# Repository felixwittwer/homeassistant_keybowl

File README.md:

<br>

<div align="center">

 &nbsp; &nbsp; 

</div>

<br>

# homeassistant_keybowl
a smart bowl for your keys with Homeassistant integration and a display to show simple dashoards.

## About the project

This project is smart keybowl where you can toss all your keys into and it will show you some interesting stuff from your Homeassistant instance. It simply hits you with the information you need when leaving home or comming back. The shown dashboards are custom for each user and are recognised by the RFID tag on each keychain.

The Keybowl should speed up your everyday routine by presenting you all the information you might have to look up in some app on your phone. For me personally my dashboard will contain a short version of the days timetable for school and its current changes for the day. When comming home it will probably display some stats of my servers.

The Keybowl siply will be a smart everday helper to make my and the life of others a bit easier and reduce the time you have to look up some information on your phone.

## The Project

### PCB

Be aware that some parts on the rende will not be populated on the PCB because they are not really needed but may be in the future or while I am building the project so for futureprovness the are on in the pcb design and in the rendered images. Have a look at the BOM so se which parts are ment and be aware to bridge the if they are not populated.

### complete assembly

A screenshot of the whole project. Sorry no beautiful render fusions standard wood textures look just ugly :(.

### CAD 

All CAD files can be found inside the [cad](./cad/) directory

[keybowl_complete](./cad/Keybowl%20complete.step) is the whole project and the other files are individual parts of the complete project.

### Firmware

Detailed instructions on how to setup the firmware can be found inside the [firmware folders README](./firmware/README.md)

## BOM

### Aliexpress (for Highway)

**total:** 141.60 USD

| part name | amount | price | link | note |
| --------- | ------ | ----- | ---- | ---- |
| UHF RFID Module 1dbi 35x35mm | 1 | 39.27 USD | https://de.aliexpress.com/item/1005008307223636.html?spm=a2g0o.productlist.main.2.3a2056acCbDovs&algo_pvid=561ac428-5895-4565-92d7-d20539900a0c&pdp_ext_f=%7B%22order%22%3A%228%22%2C%22eval%22%3A%221%22%7D&utparam-url=scene%3Asearch%7Cquery_from%3A | |
| 4.2inch e-paper | 1 | 29.38 USD | https://de.aliexpress.com/item/1005005825856739.html?spm=a2g0o.productlist.main.11.398af4a457pUEA&algo_pvid=a1b8dab7-90ac-46bd-aca0-fde6fcd30138&pdp_ext_f=%7B%22order%22%3A%2213%22%2C%22eval%22%3A%221%22%7D&utparam-url=scene%3Asearch%7Cquery_from%3A | would have liked to choose another one but waveshare has the best documentation and if you decide to upgrade the displays have the same footprint (upgrading from 4 grayscale to black/white/red possible)|
| Raspberry Pi Zero 2 W | 1 | 20.57 USD | https://de.aliexpress.com/item/1005008147614202.html?spm=a2g0o.productlist.main.9.1e3f432ciKsp9W&algo_pvid=32a8750d-1fe9-43b5-99b0-1ed1efdb7aec&pdp_ext_f=%7B%22order%22%3A%22141%22%2C%22eval%22%3A%221%22%7D&utparam-url=scene%3Asearch%7Cquery_from%3A | Pi Zero needed because of Homeassistant integration and connectivity (ESP32-S3 can't quite manage all this stuff together) |
| RFID tags | 5pcs | 0.99 USD | https://de.aliexpress.com/item/1005008292479936.html?spm=a2g0o.productlist.main.45.186a419cIs6EWx&algo_pvid=f2a1d2c4-8d39-4e0e-816f-0145ab5a5fc3&pdp_ext_f=%7B%22order%22%3A%2224%22%2C%22eval%22%3A%221%22%7D&utparam-url=scene%3Asearch%7Cquery_from%3A
| keyswitches | 6 | 1.19 USD | https://de.aliexpress.com/item/1005005371211477.html?spm=a2g0o.productlist.main.6.79e64294kL6s5H&algo_pvid=e22f25ac-00f0-4e9f-a177-d081d068b5ac&pdp_ext_f=%7B%22order%22%3A%2213%22%2C%22eval%22%3A%221%22%7D&utparam-url=scene%3Asearch%7Cquery_from%3A | come as 10 pcs set |
| basic DSA Keycaps | 6 | 1.19 USD | https://de.aliexpress.com/item/1005006005905021.html?spm=a2g0o.productlist.main.11.3fe97aeaDABDMY&algo_pvid=8be567c0-1498-4e45-9ebd-240fe64a8e61&pdp_ext_f=%7B%22order%22%3A%22525%22%2C%22eval%22%3A%221%22%7D&utparam-url=scene%3Asearch%7Cquery_from%3A | come as 20 pcs set |
| PCB and PCBA | 1 | ~ 50 USD |  https://jlcpcb.com/ | price is subject to JLCs review |

**--- PCB Assembly stuff if you want to populate yourself (prices from JLC PCBA) ---**
| part name | amount | price | link | note |
| --------- | ------ | ----- | ---- | ---- |
| capacitor 0.1 uF | 9 | $0.1254 | https://jlcpcb.com/partdetail/C30926 | ---- |
| WS2812B LEDs | 9 | $2.3471 | https://jlcpcb.com/partdetail/C2843785 | ---- |
| diodes | 6 | $0.4644 | https://jlcpcb.com/partdetail/C24372 | ---- |
| | total | 2,9369 USD

<br>
optional parts (will not be populated) keep in mind to bridge footprints

| part name | amount | price | link | note |
| --------- | ------ | ----- | ---- | ---- |
| capacitor 10uF  | 1 | $0.1098 | https://jlcpcb.com/partdetail/C39060 | ---- |
| Levelshifter 74AHCT1G125 | 1 | $0.3820 | https://jlcpcb.com/partdetail/C842287 | ---- |
| Resistor 470 ohm | 9 | $0.0300 | https://jlcpcb.com/partdetail/C21266 | ---- |
| usb-c connector | 1 | 0.99 USD | https://de.aliexpress.com/item/1005008164395076.html?spm=a2g0o.productlist.main.5.3a0390d4i1qG9U&algo_pvid=b5963a54-6f39-4deb-8dc8-244e51b0128a&pdp_ext_f=%7B%22order%22%3A%2252%22%2C%22eval%22%3A%221%22%7D&utparam-url=scene%3Asearch%7Cquery_from%3A | ----
| | total | 1,5118 USD

**total:** 141.60 USD

<br>
<br>
for people who don't want to order via aliexpress or simply can't here is a BOM with mostly amazon equivalients

### Amazon (mostly)

**total:** 192.48 USD

| part name | amount | price | link | note |
| --------- | ------ | ----- | ---- | ---- |
| UHF RFID Module 1dbi 35x35mm | 1 | 39.27 USD | https://de.aliexpress.com/item/1005008307223636.html?spm=a2g0o.productlist.main.2.3a2056acCbDovs&algo_pvid=561ac428-5895-4565-92d7-d20539900a0c&pdp_ext_f=%7B%22order%22%3A%228%22%2C%22eval%22%3A%221%22%7D&utparam-url=scene%3Asearch%7Cquery_from%3A | | 
| 4.2inch e-paper | 1 | 54.08 USD | https://www.amazon.de/dp/B074NR1SW2?ref=nb_sb_ss_w_as-reorder_k0_1_14&amp=&crid=2M3OI3RSIFS23&amp=&sprefix=waveshare+4.2+ | would have liked to choose another one but waveshare has the best documentation and if you decide to upgrade the displays have the same footprint (upgrading from 4 grayscale to black/white/red possible)| 
| Raspberry Pi Zero 2 W | 1 | 26.93 USD | https://www.amazon.de/Raspberry-Pi-Zero-2-W/dp/B09KLVX4RT/ref=sr_1_4?crid=3F4JLZT8J09I2&dib=eyJ2IjoiMSJ9.fncIJs8H7j2XX5cd0eT7dzY-YB1tPbo4gCqagVr8h4DMTsPONH_Mult_7ijuBQ3GCfVFECBAdYaNTrHF1bfQANcU2Pdy5dbgRbXKhRWFQr8cmPsjBGjKH1krP5Ws6mtLZLUshB_XdoqjZr_CAx5a_L92mJQcLqmJuna4ZfHLp4acVftQ5eg-PrHAdllF9GTtD_eJ6C1KdjmjpKIULVyuFIdfxD1z5jvnKwc3p1OkQ1Jg8JrRrnfVP0yk4XQYeFaaPV2xwpZcc07g_3GJIsN3DBhpj1nk5DgTsJjX4YznR2k.yyQFt7UIPqDHxDQO8hu-LWC2HYWDHKguauu7Td6Olso&dib_tag=se&keywords=raspberry+pi+zero+2+w&qid=1753744983&s=ce-de&sprefix=Raspberry+pi+zero+%2Celectronics%2C98&sr=1-4 | Pi Zero needed because of Homeassistant integration and connectivity (ESP32-S3 can't quite manage all this stuff together) |
| RFID tags | 5pcs | 7.95 USD | https://www.amazon.de/YARONGTECH%C2%AE-RFID-13-56-MIFARE-Classic/dp/B0749LSMLH/ref=sxin_14_pa_sp_search_thematic_sspa?content-id=amzn1.sym.a242ad73-69d0-4a8d-978f-6d53f9236b99%3Aamzn1.sym.a242ad73-69d0-4a8d-978f-6d53f9236b99&cv_ct_cx=UHF%2BRFID%2BTags&keywords=UHF%2BRFID%2BTags&pd_rd_i=B0749LSMLH&pd_rd_r=0e00a4a4-8c83-4ebc-ac8e-bae66742f21d&pd_rd_w=6j0Rf&pd_rd_wg=HciHT&pf_rd_p=a242ad73-69d0-4a8d-978f-6d53f9236b99&pf_rd_r=VQ0N5YRANKXCNTZ7MPBB&qid=1753745046&sbo=RZvfv%2F%2FHxDF%2BO5021pAnSA%3D%3D&sr=1-4-6e6ea531-5af4-4866-af75-1ef299d1c279-spons&sp_csd=d2lkZ2V0TmFtZT1zcF9zZWFyY2hfdGhlbWF0aWM&th=1
| keyswitches | 6 | 8.55 USD | https://www.amazon.de/Topiky-mechanische-Tastatur-Schalter-RGB-Serie-default/dp/B07Q6YJ2GS/ref=sr_1_4?__mk_de_DE=%C3%85M%C3%85%C5%BD%C3%95%C3%91&crid=2HGLC4FVRGMVT&dib=eyJ2IjoiMSJ9.lr5pAyALa6zcpgvL6ocizh29OOdjswZu4E4GeYNoWHIvrGlExXAwSyftE1IDWQx-MioXa6eRHgOxY2aw3guxSyAhm1cRLiGjPbMxXagl5DVjl8zlA3-Fq1xMeFf0keuf6sWMwxEs4qJEJFuOrQp60NqdRFE5JP7ZUXHdBS8-ciUZ8sUM1v-SfSSCQGwi5z9b3cOaczM_vdHGwrK4-27L5SMwiXW614olzfLW9IitxVc.iKE2S4eT_9iuzVTC6o7dY5whqCbZ38v4vOEYg8mp4xU&dib_tag=se&keywords=key+switches+10pcs&qid=1753745144&sprefix=keyswitches+10pcs%2Caps%2C112&sr=8-4 | come as 10 pcs set |
| basic DSA Keycaps | 6 | 5.70 USD | https://www.amazon.de/Transparent-Keycaps-Mechanical-Keyboard-Clearance/dp/B0CJLS9GGP/ref=sr_1_19?__mk_de_DE=%C3%85M%C3%85%C5%BD%C3%95%C3%91&crid=3CAQ81AOP2M92&dib=eyJ2IjoiMSJ9.G0fOvRvtEiZgcqpE2Wc206IvnsBJ5Jrvxn1RmotGQ7HUJCprLko5q7wVfJI7415UhvwI3se32bR2nUqGuKlnGvhHhfeHqy9B4esfWzyFa4EJRnYLoMsVAdIpiB40xEuWyPwM6HeskDKa0agOa41NRN_B-0KzamPvFWs3T6iy9GN3KRjpukQTlhsooCbJO57FyA70zvGMO-Zw8YAZ9qUnXQFgg3Sf7knfkXQ-GAE1B20.NdI2huIxU0bxjYP2Cydikf1cZd7J_cRb7I6SJbThV_o&dib_tag=se&keywords=blank+dsa+keycaps+10pcs&qid=1753745201&sprefix=blank+dsa+keycaps+10pcs%2Caps%2C95&sr=8-19 | come as 10 pcs set |
| PCB and PCBA | 1 | ~ 50 USD |  https://jlcpcb.com/ | price is subject to JLCs review |

**total:** 192.48 USD

## Credits

Raspberry Pi Zero Symbol, Footprint and 3D-Model for KiCad: https://www.snapeda.com/parts/RASPBERRY%20PI%20ZERO%202%20W/Raspberry%20Pi/view-part/?welcome=home

Waveshare 4.2inch e-Paper Module CAD: https://grabcad.com/library/waveshare-4-2-e-paper-module-1

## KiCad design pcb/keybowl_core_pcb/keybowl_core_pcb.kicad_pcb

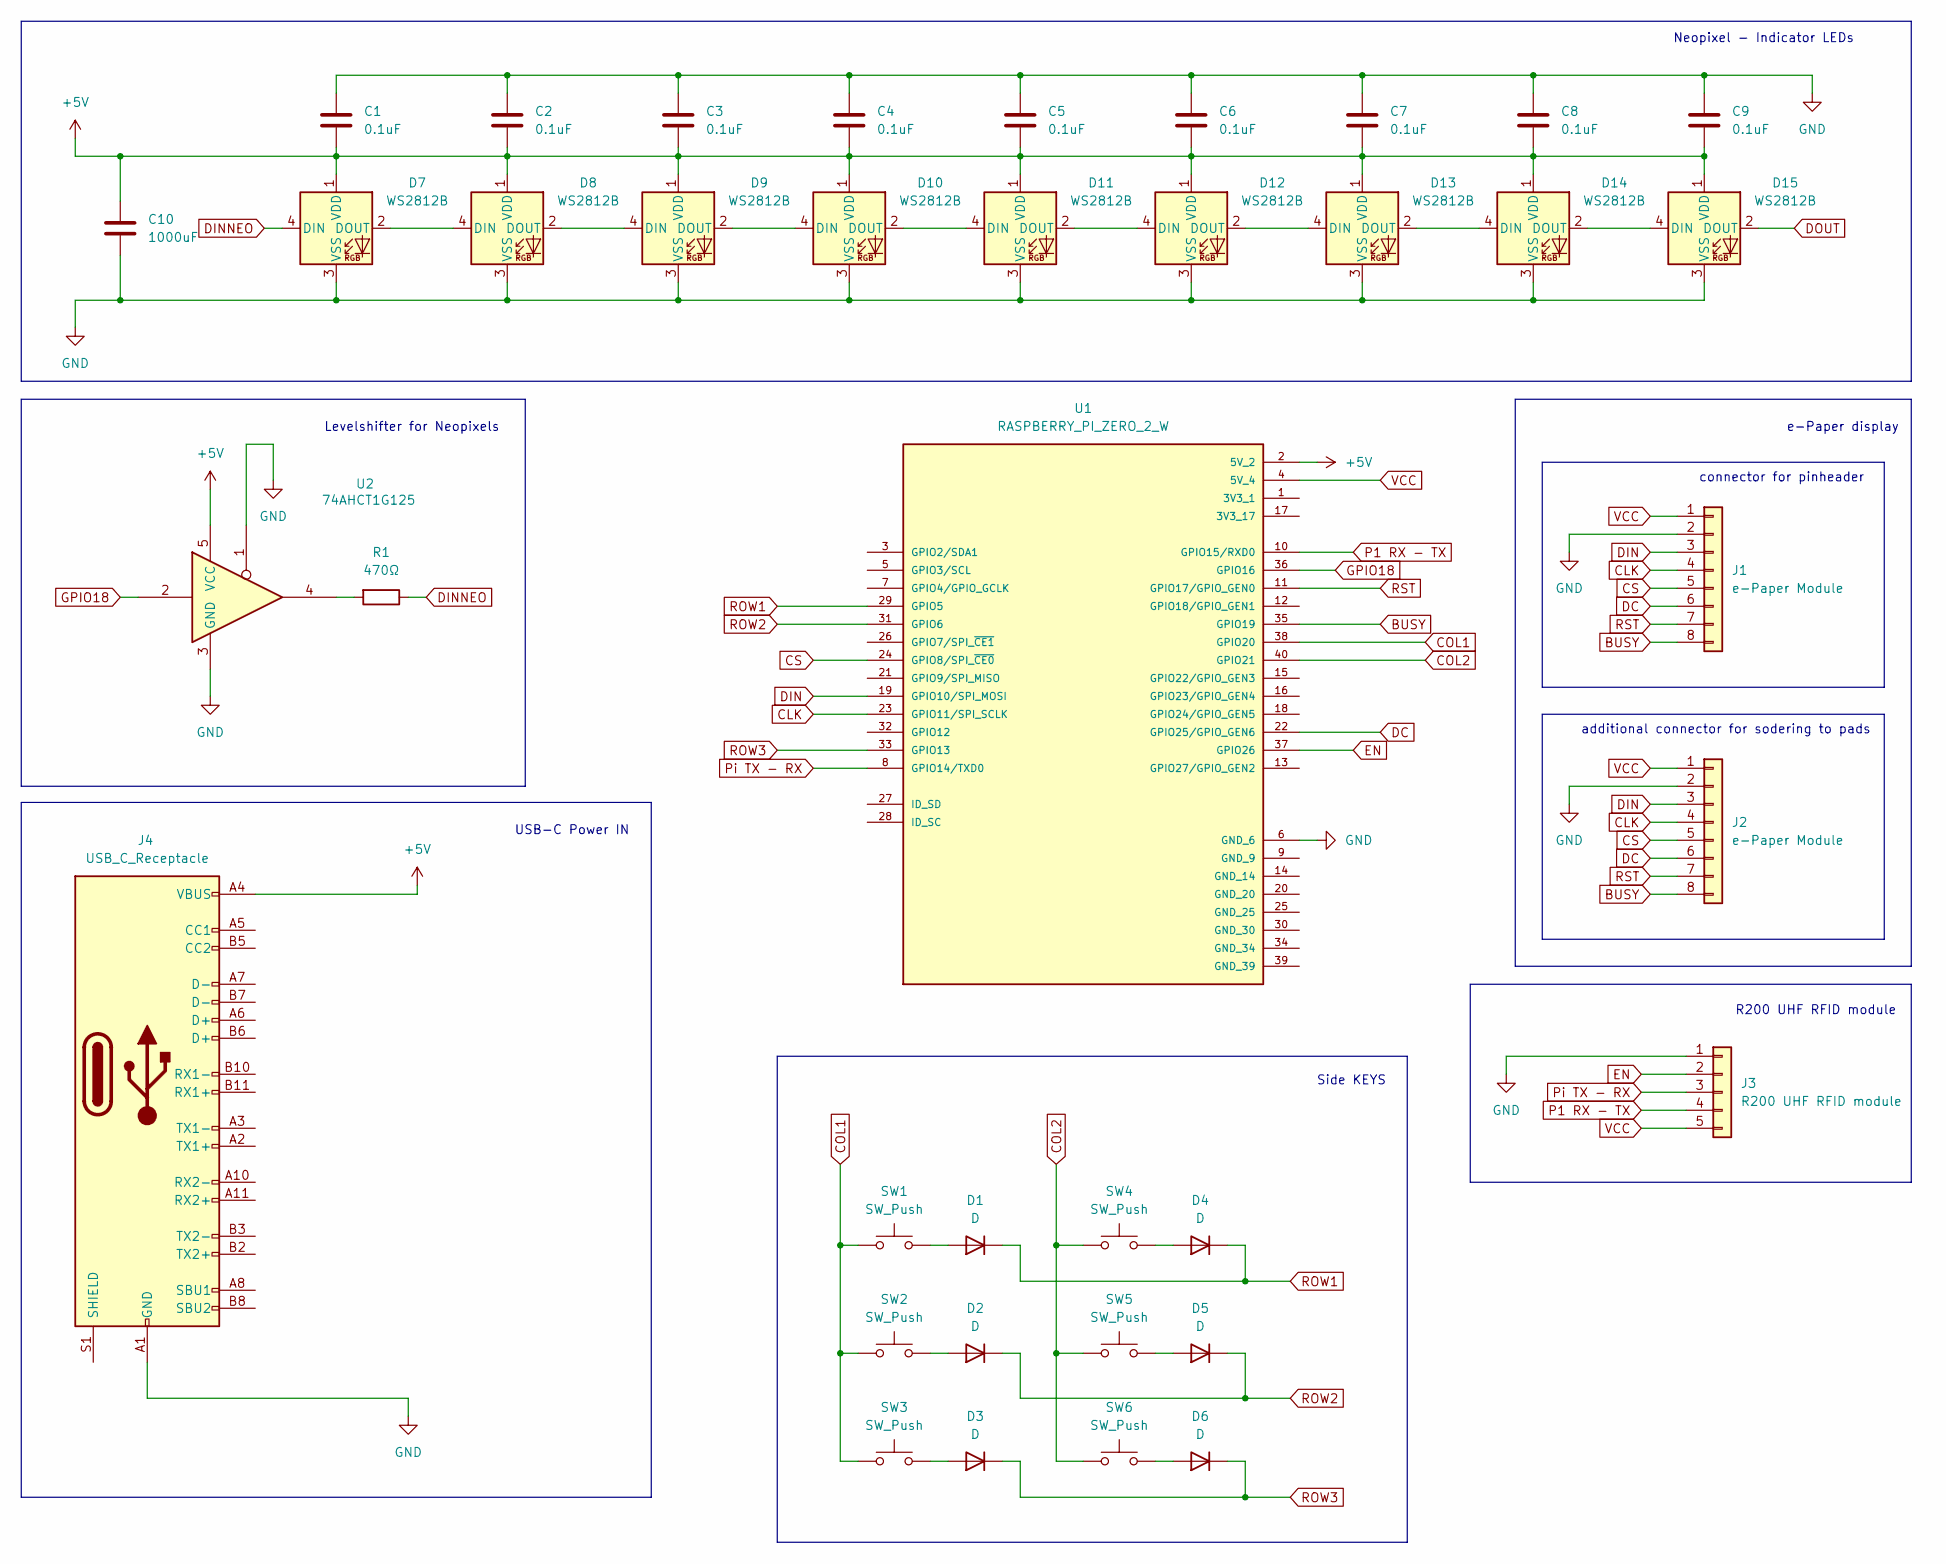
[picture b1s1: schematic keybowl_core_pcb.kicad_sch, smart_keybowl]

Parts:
C1, C2, C3, C4, C5, C6, C7, C8, C9: 0.1uF; C_0805_2012Metric
C10: 1000uF; C_0805_2012Metric
D1, D2, D3, D4, D5, D6: D; D_0805_2012Metric
D7, D8, D9, D10, D11, D12, D13, D14, D15: WS2812B; LED_WS2812B_PLCC4_5.0x5.0mm_P3.2mm
J1, J2: e-Paper Module; JST_EH_B8B-EH-A_1x08_P2.50mm_Vertical
J3: R200 UHF RFID module; JST_EH_B5B-EH-A_1x05_P2.50mm_Vertical
J4: USB_C_Receptacle; USB_C_Receptacle_GCT_USB4105-xx-A_16P_TopMnt_Horizontal
R1: 470Ω; R_0805_2012Metric_Pad1.20x1.40mm_HandSolder
SW1, SW2, SW3, SW4, SW5, SW6: SW_Push; SW_Cherry_MX_1.00u_PCB
U1: RASPBERRY_PI_ZERO_2_W; Raspberry_Pi_Zero_Socketed_THT_FaceDown_MountingHoles; PARTREV April 2024
U2: 74AHCT1G125; SOT95P280X145-5N

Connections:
+5V: C1.2, C2.2, C3.2, C4.2, C5.2, C6.2, C7.2, C8.2, C9.2, C10.1, D7.1 (VDD), D8.1 (VDD), D9.1 (VDD), D10.1 (VDD), D11.1 (VDD), D12.1 (VDD), D13.1 (VDD), D14.1 (VDD), D15.1 (VDD), J4.A4 (VBUS), J4.A9 (VBUS), J4.B4 (VBUS), J4.B9 (VBUS), U1.2 (5V_2), U2.5 (VCC)
BUSY: J1.8, J2.8, U1.35 (GPIO19)
CLK: J1.4, J2.4, U1.23 (GPIO11/SPI_SCLK)
COL1: SW1.1, SW2.1, SW3.1, U1.38 (GPIO20)
COL2: SW4.1, SW5.1, SW6.1, U1.40 (GPIO21)
CS: J1.5, J2.5, U1.24 (GPIO8/SPI_~CE0)
DC: J1.6, J2.6, U1.22 (GPIO25/GPIO_GEN6)
DIN: J1.3, J2.3, U1.19 (GPIO10/SPI_MOSI)
DINNEO: D7.4 (DIN), R1.1
DOUT: D15.2 (DOUT)
EN: J3.2, U1.37 (GPIO26)
GND: C1.1, C2.1, C3.1, C4.1, C5.1, C6.1, C7.1, C8.1, C9.1, C10.2, D7.3 (VSS), D8.3 (VSS), D9.3 (VSS), D10.3 (VSS), D11.3 (VSS), D12.3 (VSS), D13.3 (VSS), D14.3 (VSS), D15.3 (VSS), J1.2, J2.2, J3.1, J4.A1 (GND), J4.A12 (GND), J4.B1 (GND), J4.B12 (GND), U1.6 (GND_6), U2.1, U2.3 (GND)
GPIO18: U1.36 (GPIO16), U2.2
unnamed: D1.2 (A), SW1.2
unnamed: D2.2 (A), SW2.2
unnamed: D3.2 (A), SW3.2
unnamed: D4.2 (A), SW4.2
unnamed: D5.2 (A), SW5.2
unnamed: D6.2 (A), SW6.2
unnamed: D7.2 (DOUT), D8.4 (DIN)
unnamed: D8.2 (DOUT), D9.4 (DIN)
unnamed: D9.2 (DOUT), D10.4 (DIN)
unnamed: D10.2 (DOUT), D11.4 (DIN)
unnamed: D11.2 (DOUT), D12.4 (DIN)
unnamed: D12.2 (DOUT), D13.4 (DIN)
unnamed: D13.2 (DOUT), D14.4 (DIN)
unnamed: D14.2 (DOUT), D15.4 (DIN)
unnamed: R1.2, U2.4
P1 RX - TX: J3.4, U1.10 (GPIO15/RXD0)
Pi TX - RX: J3.3, U1.8 (GPIO14/TXD0)
ROW1: D1.1 (K), D4.1 (K), U1.29 (GPIO5)
ROW2: D2.1 (K), D5.1 (K), U1.31 (GPIO6)
ROW3: D3.1 (K), D6.1 (K), U1.33 (GPIO13)
RST: J1.7, J2.7, U1.11 (GPIO17/GPIO_GEN0)
VCC: J1.1, J2.1, J3.5, U1.4 (5V_4)

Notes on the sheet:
R200 UHF RFID module
connector for pinheader
Side KEYS
Levelshifter for Neopixels
USB-C Power IN
Neopixel - Indicator LEDs
additional connector for sodering to pads
e-Paper display

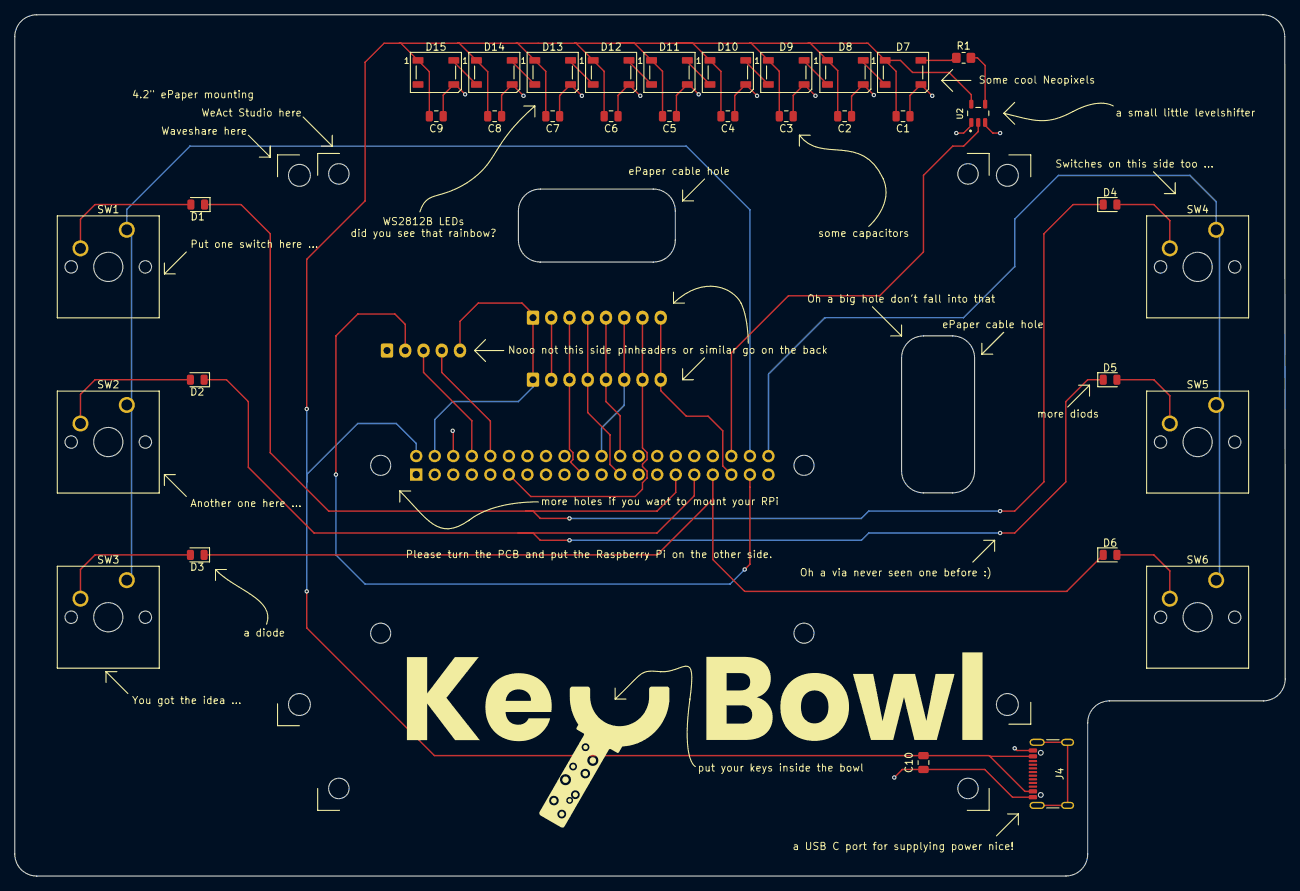
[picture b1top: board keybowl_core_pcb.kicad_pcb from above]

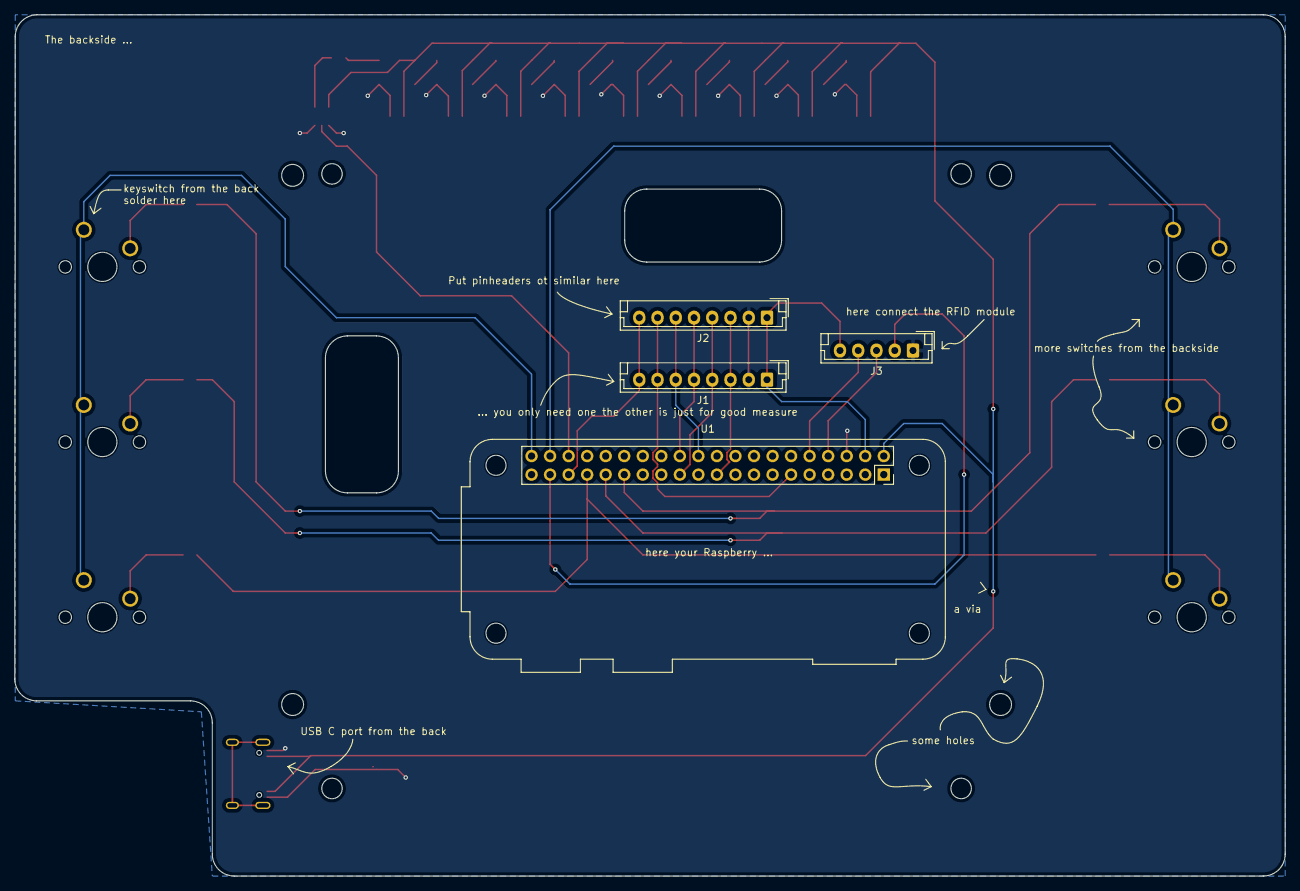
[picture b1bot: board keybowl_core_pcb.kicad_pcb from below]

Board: 2 copper layers, 174.0 x 117.9 mm, 38 parts (4 on the bottom side), 34 nets.

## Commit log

2025-07-06 start adding pcb
2025-07-08 adding branding
2025-07-08 working on pcb
2025-07-18 add assembled pcb
2025-07-19 add housing and mounting
2025-07-19 add prduction files and instructions - instructions on building the wooden base
2025-07-28 adding firmware and fix small issue inside schematic
2025-07-29 getting ready for submission
2025-07-29 getting really ready for submission
2025-07-29 small chnages on the pcb and extend BOM to PCB assembly parts
2025-07-29 fix typo
2025-07-29 add hint for unpopulated PCB parts
